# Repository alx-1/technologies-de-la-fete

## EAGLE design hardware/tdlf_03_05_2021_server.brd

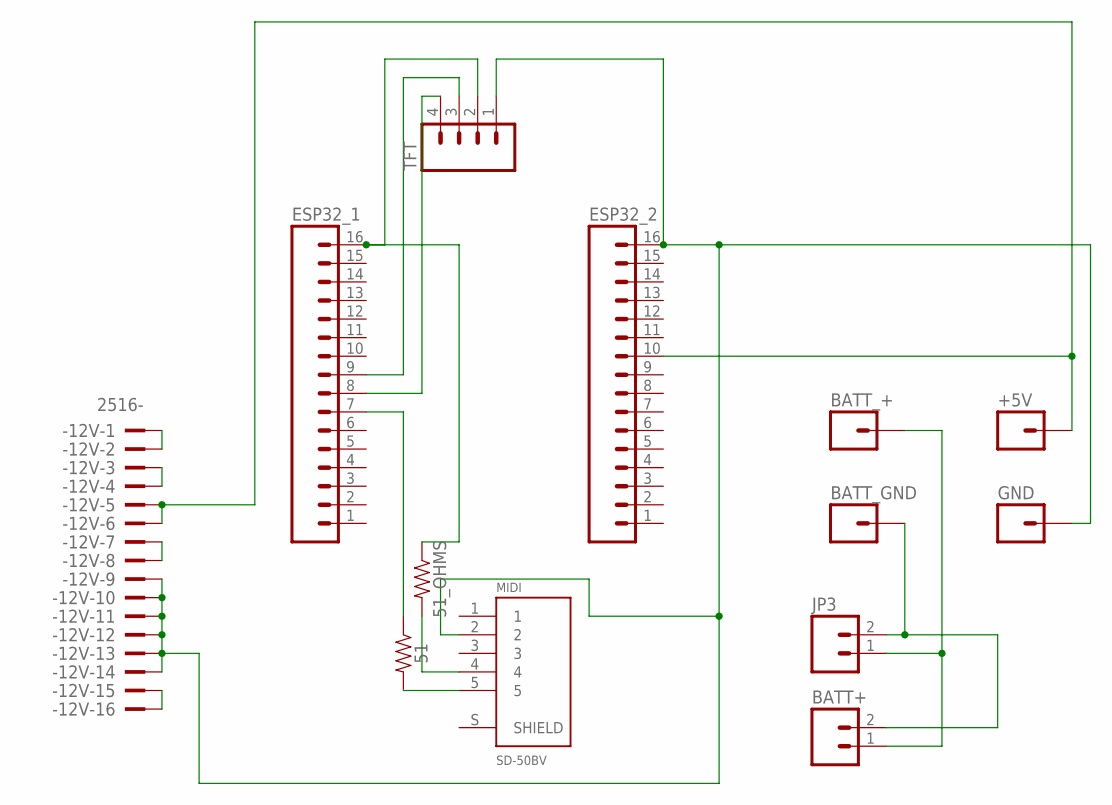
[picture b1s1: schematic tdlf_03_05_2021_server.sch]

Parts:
51, 51_OHMS: 1206
+5V: M01PTH; 1X01
-12V: 2516-; PAK100/2500-16
BATT+: M02PTH; 1X02
BATT_+: M01PTH; 1X01
BATT_GND: M01PTH; 1X01
ESP32_1, ESP32_2: M16PTH; 1X16
GND: M01PTH; 1X01
JP3: M02PTH; 1X02
MIDI: SD-50BV; CUI_SD-50BV
TFT: M04PTH; 1X04

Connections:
3V: 51_OHMS.2, MIDI.4
3V3: 51_OHMS.1, ESP32_1.16, TFT.2
5V: +5V.1, -12V.5, -12V.6, ESP32_2.10
+12V: -12V.7, -12V.8
+VBATT: BATT+.2, BATT_GND.1, JP3.2
-12V: -12V.15, -12V.16
GND: -12V.9, -12V.10, -12V.11, -12V.12, -12V.13, -12V.14, ESP32_2.16, GND.1, MIDI.2, TFT.1
GND_BATT: BATT+.1, BATT_+.1, JP3.1
unnamed: ESP32_1.9, TFT.3
unnamed: ESP32_1.8, TFT.4
unnamed: 51.1, ESP32_1.7
unnamed: -12V.1, -12V.2
unnamed: -12V.3, -12V.4
PIN27: 51.2, MIDI.5

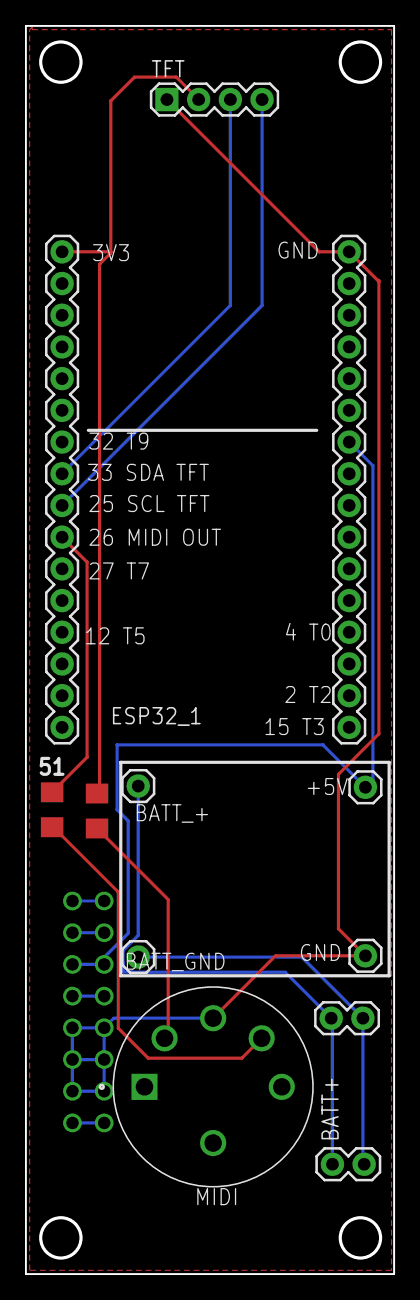
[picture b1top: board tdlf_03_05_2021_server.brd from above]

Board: 2 copper layers, 29.5 x 100.0 mm, 13 parts (1 on the bottom side), 14 nets.

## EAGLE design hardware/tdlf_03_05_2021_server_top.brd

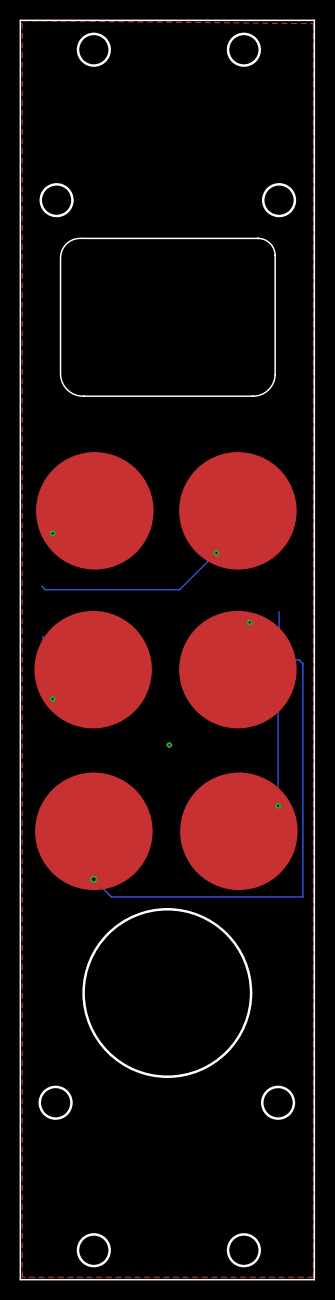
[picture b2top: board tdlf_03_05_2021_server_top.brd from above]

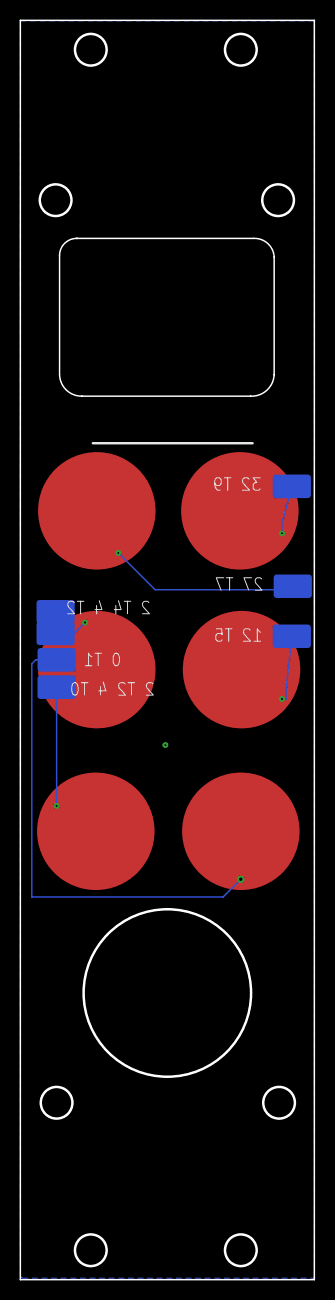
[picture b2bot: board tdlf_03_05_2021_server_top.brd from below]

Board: 2 copper layers, 30.0 x 128.5 mm, 13 parts (7 on the bottom side), 6 nets.

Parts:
CAP_MUSH: MUSH; TDLF_CAP_02
CAP_PLUS: TDLF_CAP_PLUS
JP1, JP2, JP3, JP4, JP5, JP6, JP7: LUXEON-PAD
U$1: TDLF_CAP_MOINS
U$2: TDLF_CAP_SPIRAL
U$3: TDLF_CAP_KOPIMI
U$4: TDLF_CAP_ACHTUNG

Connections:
CHAMPI: CAP_MUSH.P$1, JP1.P$1
KOPIMI: JP5.P$1, JP6.P$1, U$3.P$1
MOINS: JP2.P$1, U$1.P$1
unnamed: JP7.P$1, U$4.P$1
PLUS: CAP_PLUS.P$1, JP3.P$1
SPIRAL: JP4.P$1, U$2.P$1

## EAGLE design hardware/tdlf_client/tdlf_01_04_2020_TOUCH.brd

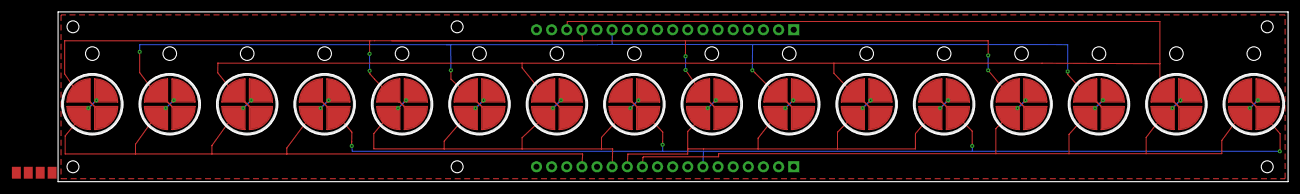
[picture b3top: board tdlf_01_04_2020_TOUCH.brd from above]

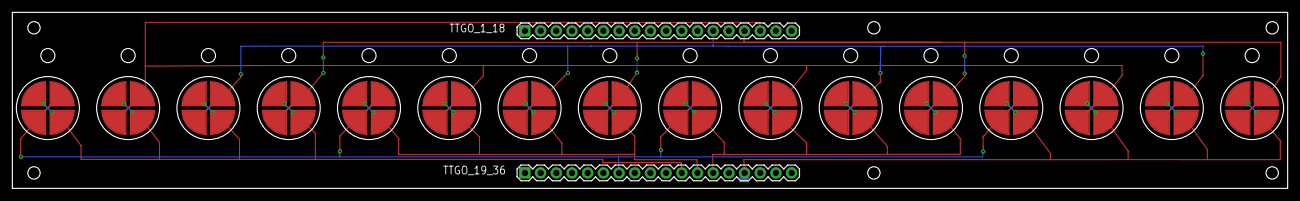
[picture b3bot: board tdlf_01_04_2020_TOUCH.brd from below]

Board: 2 copper layers, 206.5 x 28.5 mm, 23 parts (3 on the bottom side), 8 nets.

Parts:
JP1: 27_T7; PAD-1.5X4.5
JP2: 32_T9; PAD-1.5X4.5
JP3: 14_T6; PAD-1.5X4.5
JP4: 12_T5; PAD-1.5X4.5
JP5: 13_T4; PAD-1.5X4.5
S1, S2, S3, S4, S5, S6, S7, S8, S9, S10, S11, S12, S13, S14, S15, S16: R1206
TTGO_1_18, TTGO_19_36: 1X18

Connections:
TOUCH1_0: S2.P$1, S2.P$5, S6.P$1, S6.P$5, S10.P$1, S10.P$5, S14.P$1, S14.P$5, TTGO_1_18.13
TOUCH2_2: S1.P$1, S1.P$5, S5.P$1, S5.P$5, S9.P$1, S9.P$5, S13.P$1, S13.P$5, TTGO_1_18.15
TOUCH3_15: S3.P$1, S3.P$5, S7.P$1, S7.P$5, S11.P$1, S11.P$5, S15.P$1, S15.P$5, TTGO_1_18.16
TOUCH4_13: JP2.P$1, S4.P$1, S4.P$5, S8.P$1, S8.P$5, S12.P$1, S12.P$5, S16.P$1, S16.P$5, TTGO_19_36.7
TOUCH5_12: JP1.P$1, S13.P$2, S14.P$2, S15.P$2, S16.P$2, TTGO_19_36.11
TOUCH6_14: JP3.P$1, S9.P$2, S10.P$2, S11.P$2, S12.P$2, TTGO_19_36.12
TOUCH7_27: JP4.P$1, S5.P$2, S6.P$2, S7.P$2, S8.P$2, TTGO_19_36.13
TOUCH9_32: JP5.P$1, S1.P$2, S2.P$2, S3.P$2, S4.P$2, TTGO_19_36.15

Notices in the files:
parts and their libraries:
SparkFun-Connectors: Licensing: Creative Commons ShareAlike 4.0 International - https://creativecommons.org/licenses/by-sa/4.0
